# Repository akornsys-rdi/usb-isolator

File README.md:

# usb-isolator
Simple full speed usb isolator as host protection

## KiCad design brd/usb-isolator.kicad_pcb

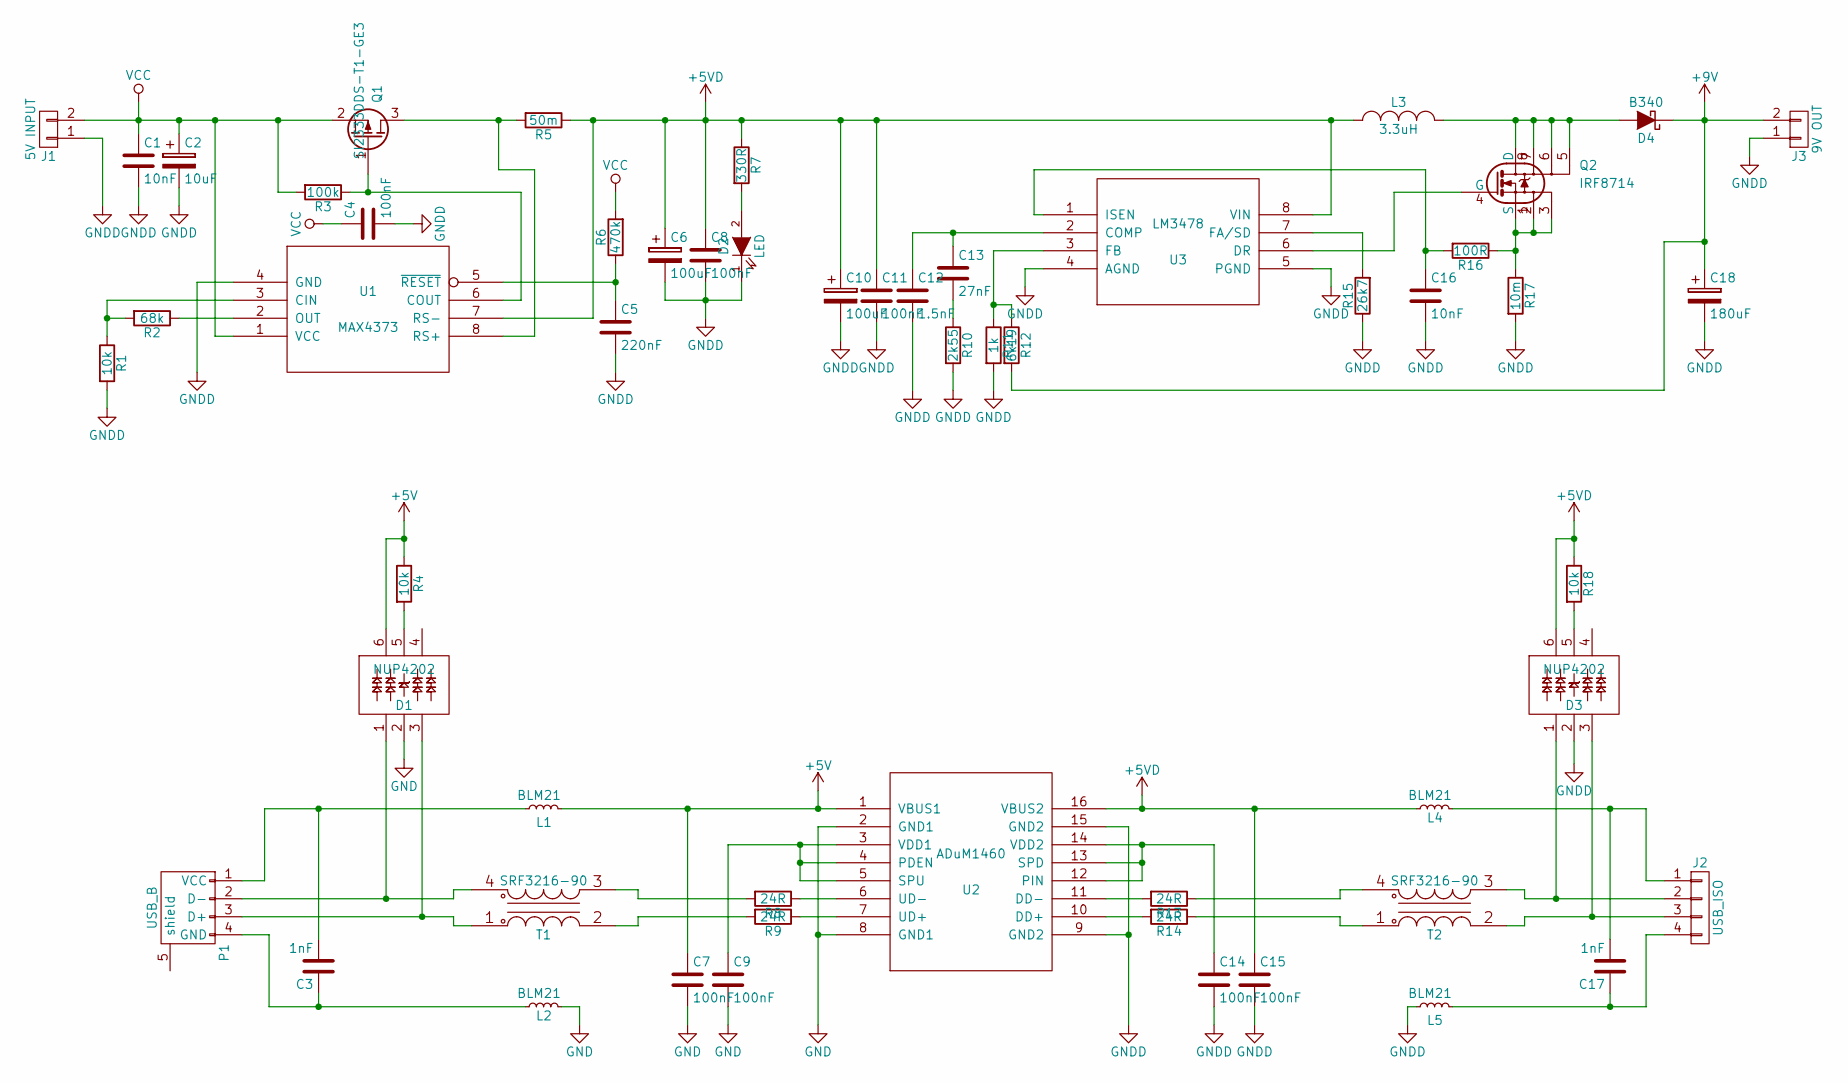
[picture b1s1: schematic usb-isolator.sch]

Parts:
C1, C16: 10nF; C_0805_HandSoldering
C2: 10uF; c_elec_4x5.3
C3, C17: 1nF; C_0805_HandSoldering
C4, C7, C8, C9, C11, C14, C15: 100nF; C_0805_HandSoldering
C5: 220nF; C_0805_HandSoldering
C6: 100uF; c_elec_6.3x5.3
C10: 100uF; TantalC_SizeB_EIA-3528_HandSoldering
C12: 1.5nF; C_0805_HandSoldering
C13: 27nF; C_0805_HandSoldering
C18: 180uF; c_elec_6.3x5.8
D1, D3: NUP4202; SC-70-6_Handsoldering
D2: LED; LED-0805
D4: B340; Diode-SMA_Handsoldering
J1: 5V INPUT; bornier2
J2: USB_ISO
J3: 9V OUT
L1, L2, L4, L5: BLM21; R_0805_HandSoldering
L3: 3.3uH; coil-13x13H7
P1: USB_B; USB_Mini-B
Q1: SI2333DDS-T1-GE3; SOT-23_Handsoldering
Q2: IRF8714; SOIC-8_3.9x4.9mm_Pitch1.27mm
R1, R4, R18: 10k; R_0805_HandSoldering
R2: 68k; R_0805_HandSoldering
R3: 100k; R_0805_HandSoldering
R5: 50m; R_2512_HandSoldering
R6: 470k; R_0805_HandSoldering
R7: 330R; R_0805_HandSoldering
R8, R9, R13, R14: 24R; R_0805_HandSoldering
R10: 2k55; R_0805_HandSoldering
R11: 1k; R_0805_HandSoldering
R12: 6k19; R_0805_HandSoldering
R15: 26k7; R_0805_HandSoldering
R16: 100R; R_0805_HandSoldering
R17: 10m; 0612
T1, T2: SRF3216-90; Choke-SRF3216
U1: MAX4373; SOIC-8_3.9x4.9mm_Pitch1.27mm
U2: ADuM1460; SOIC-16_7.5x10.3mm_Pitch1.27mm
U3: LM3478; MSOP-8_3x3mm_Pitch0.65mm

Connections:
+5V: C7.1, D1.6, L1.2, R4.1, U2.1 (VBUS1)
+5VD: C6.1, C8.1, C10.1, C11.1, C15.1, D3.6, L3.1, L4.1, R5.1, R7.1, R18.1, U1.7 (RS-), U2.16 (VBUS2), U3.8 (VIN)
+9V: C18.1, D4.1 (K), J3.2, R12.2
GND: C7.2, C9.2, D1.2, L2.2, U2.2 (GND1), U2.8 (GND1)
GNDD: C1.2, C2.2, C4.2, C5.2, C6.2, C8.2, C10.2, C11.2, C12.2, C14.2, C15.2, C16.2, C18.2, D2.1 (K), D3.2, J1.1, J3.1, L5.1, R1.2, R10.2, R11.2, R15.1, R17.2, U1.4 (GND), U2.9 (GND2), U2.15 (GND2), U3.4 (AGND), U3.5 (PGND)
unnamed: C3.1, L2.1, P1.4 (GND)
unnamed: C3.2, L1.1, P1.1 (VCC)
unnamed: C5.1, R6.1, U1.5 (~RESET)
unnamed: C9.1, U2.3 (VDD1), U2.4 (PDEN), U2.5 (SPU)
unnamed: C12.1, C13.1, U3.2 (COMP)
unnamed: C13.2, R10.1
unnamed: C14.1, U2.12 (PIN), U2.13 (SPD), U2.14 (VDD2)
unnamed: C16.1, R16.2, U3.1 (ISEN)
unnamed: C17.1, J2.4, L5.2
unnamed: C17.2, J2.1, L4.2
unnamed: D1.1, P1.2 (D-), T1.4 (SB)
unnamed: D1.3, P1.3 (D+), T1.1 (AA)
unnamed: D1.5, R4.2
unnamed: D2.2 (A), R7.2
unnamed: D3.1, J2.2, T2.3 (SA)
unnamed: D3.3, J2.3, T2.2 (AB)
unnamed: D3.5, R18.2
unnamed: D4.2 (A), L3.2, Q2.5, Q2.6, Q2.7, Q2.8 (D)
unnamed: Q1.1 (G), R3.1, U1.6 (COUT)
unnamed: Q1.3 (D), R5.2, U1.8 (RS+)
unnamed: Q2.1 (S), Q2.2, Q2.3, R16.1, R17.1
unnamed: Q2.4 (G), U3.6 (DR)
unnamed: R1.1, R2.2, U1.3 (CIN)
unnamed: R2.1, U1.2 (OUT)
unnamed: R8.1, U2.6 (UD-)
unnamed: R8.2, T1.3 (SA)
unnamed: R9.1, U2.7 (UD+)
unnamed: R9.2, T1.2 (AB)
unnamed: R11.1, R12.1, U3.3 (FB)
unnamed: R13.1, T2.4 (SB)
unnamed: R13.2, U2.11 (DD-)
unnamed: R14.1, T2.1 (AA)
unnamed: R14.2, U2.10 (DD+)
unnamed: R15.2, U3.7 (FA/SD)
VCC: C1.1, C2.1, C4.1, J1.2, Q1.2 (S), R3.2, R6.2, U1.1 (VCC)

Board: 2 copper layers, 54 parts (1 on the bottom side), 40 nets, no tracks yet.

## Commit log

2015-12-06 new: dev: borrador !wip
